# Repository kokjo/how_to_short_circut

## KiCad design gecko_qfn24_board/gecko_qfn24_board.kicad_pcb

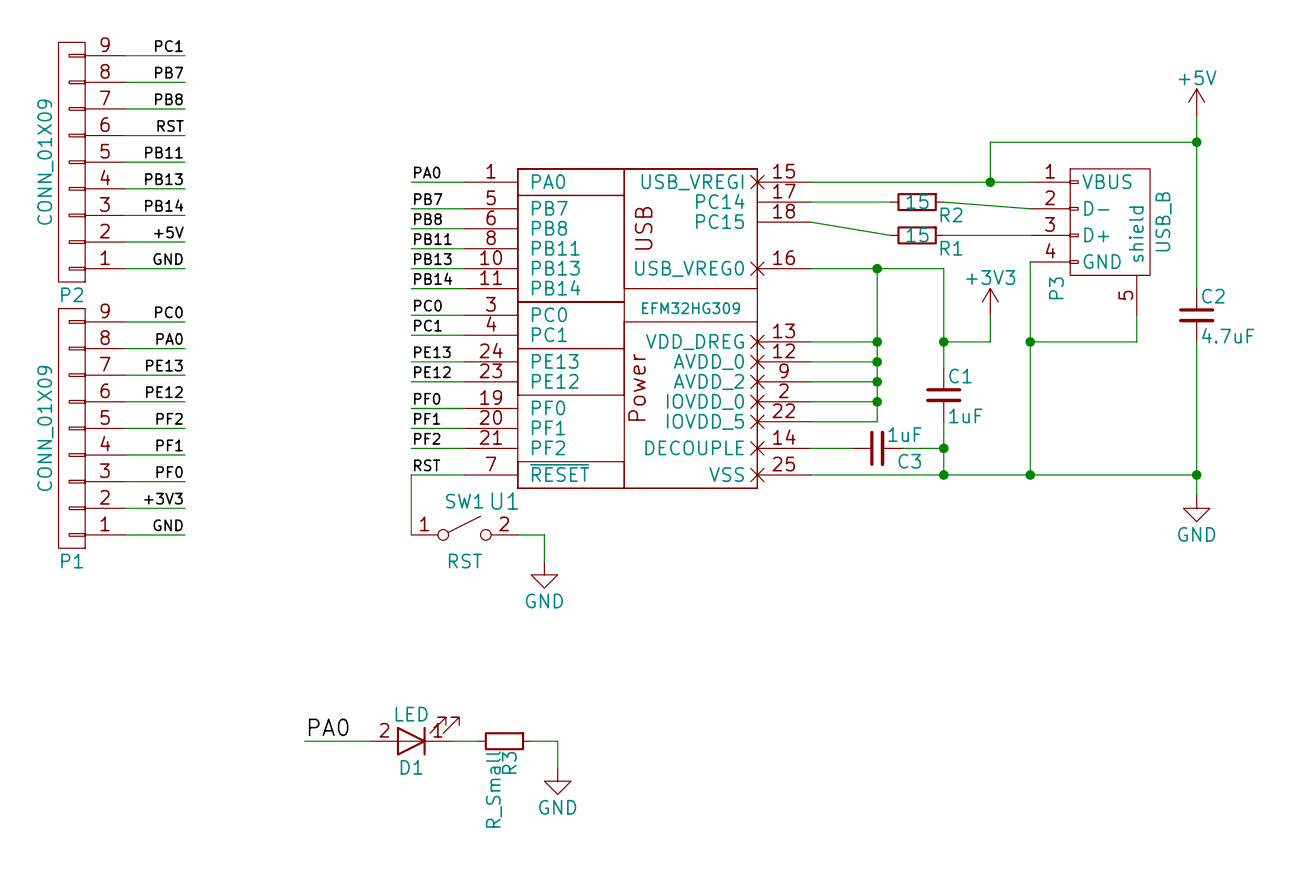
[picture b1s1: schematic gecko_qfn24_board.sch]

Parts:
C1, C3: 1uF; C_0805
C2: 4.7uF; C_0805
D1: LED; LED_0805
P1, P2: CONN_01X09; Pin_Header_Straight_1x09
P3: USB_B; USB_Micro-B_Molex_47346-0001
R1, R2: 15; R_0805
R3: R_Small; R_0805
SW1: RST; SW_SPST_B3U-1000P
U1: EFM32HG309; QFN-24-1EP_5x5mm_Pitch0.65mm

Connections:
+3V3: C1.1, P1.2, U1.2 (IOVDD_0), U1.9 (AVDD_2), U1.12 (AVDD_0), U1.13 (VDD_DREG), U1.16 (USB_VREG0), U1.22 (IOVDD_5); also elsewhere on the board
+5V: C2.1, P2.2, P3.1 (VBUS), U1.15 (USB_VREGI); also elsewhere on the board
/PA0: D1.2 (A), P1.8, U1.1 (PA0); also elsewhere on the board
/PB7: P2.8, U1.5 (PB7); also elsewhere on the board
/PB8: P2.7, U1.6 (PB8); also elsewhere on the board
/PB11: P2.5, U1.8 (PB11); also elsewhere on the board
/PB13: P2.4, U1.10 (PB13); also elsewhere on the board
/PB14: P2.3, U1.11 (PB14); also elsewhere on the board
/PC0: P1.9, U1.3 (PC0); also elsewhere on the board
/PC1: P2.9, U1.4 (PC1); also elsewhere on the board
/PE12: P1.6, U1.23 (PE12); also elsewhere on the board
/PE13: P1.7, U1.24 (PE13); also elsewhere on the board
/PF0: P1.3, U1.19 (PF0); also elsewhere on the board
/PF1: P1.4, U1.20 (PF1); also elsewhere on the board
/PF2: P1.5, U1.21 (PF2); also elsewhere on the board
/RST: P2.6, SW1.1 (A), U1.7 (~RESET); also elsewhere on the board
GND: C1.2, C2.2, C3.2, P1.1, P2.1, P3.4 (GND), P3.5 (shield), R3.1, SW1.2 (B), U1.25 (VSS); also elsewhere on the board
unnamed 17: C3.1, U1.14 (DECOUPLE); also elsewhere on the board
unnamed: D1.1 (K), R3.2
unnamed: P3.2 (D-), R2.1
unnamed: P3.3 (D+), R1.1
unnamed 21: R1.2, U1.18 (PC15); also elsewhere on the board
unnamed 22: R2.2, U1.17 (PC14); also elsewhere on the board

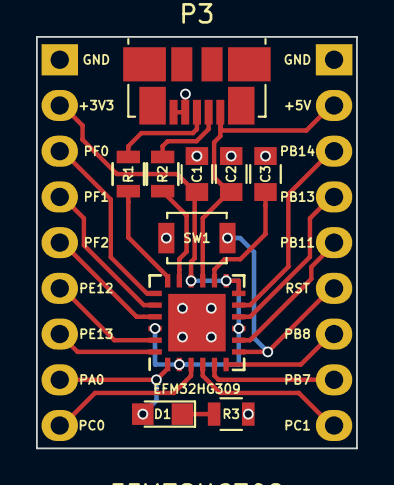
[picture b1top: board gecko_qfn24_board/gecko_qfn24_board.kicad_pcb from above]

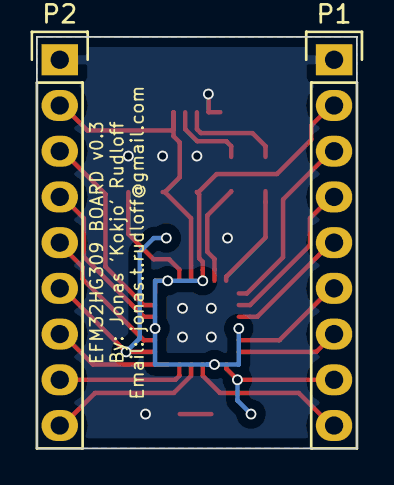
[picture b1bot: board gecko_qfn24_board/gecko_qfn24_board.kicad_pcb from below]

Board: 2 copper layers, 17.8 x 22.9 mm, 12 parts (2 on the bottom side), 23 nets.

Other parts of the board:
EFM32HG309: EFM32HG309; QFN-24-1EP_5x5mm_Pitch0.65mm

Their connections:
+3V3: EFM32HG309.2, EFM32HG309.9, EFM32HG309.12, EFM32HG309.13, EFM32HG309.16, EFM32HG309.22; also elsewhere on the board
+5V: EFM32HG309.15; also elsewhere on the board
/PA0: EFM32HG309.1; also elsewhere on the board
/PB7: EFM32HG309.5; also elsewhere on the board
/PB8: EFM32HG309.6; also elsewhere on the board
/PB11: EFM32HG309.8; also elsewhere on the board
/PB13: EFM32HG309.10; also elsewhere on the board
/PB14: EFM32HG309.11; also elsewhere on the board
/PC0: EFM32HG309.3; also elsewhere on the board
/PC1: EFM32HG309.4; also elsewhere on the board
/PE12: EFM32HG309.23; also elsewhere on the board
/PE13: EFM32HG309.24; also elsewhere on the board
/PF0: EFM32HG309.19; also elsewhere on the board
/PF1: EFM32HG309.20; also elsewhere on the board
/PF2: EFM32HG309.21; also elsewhere on the board
/RST: EFM32HG309.7; also elsewhere on the board
GND: EFM32HG309.25; also elsewhere on the board
unnamed 17: EFM32HG309.14; also elsewhere on the board
unnamed 21: EFM32HG309.18; also elsewhere on the board
unnamed 22: EFM32HG309.17; also elsewhere on the board

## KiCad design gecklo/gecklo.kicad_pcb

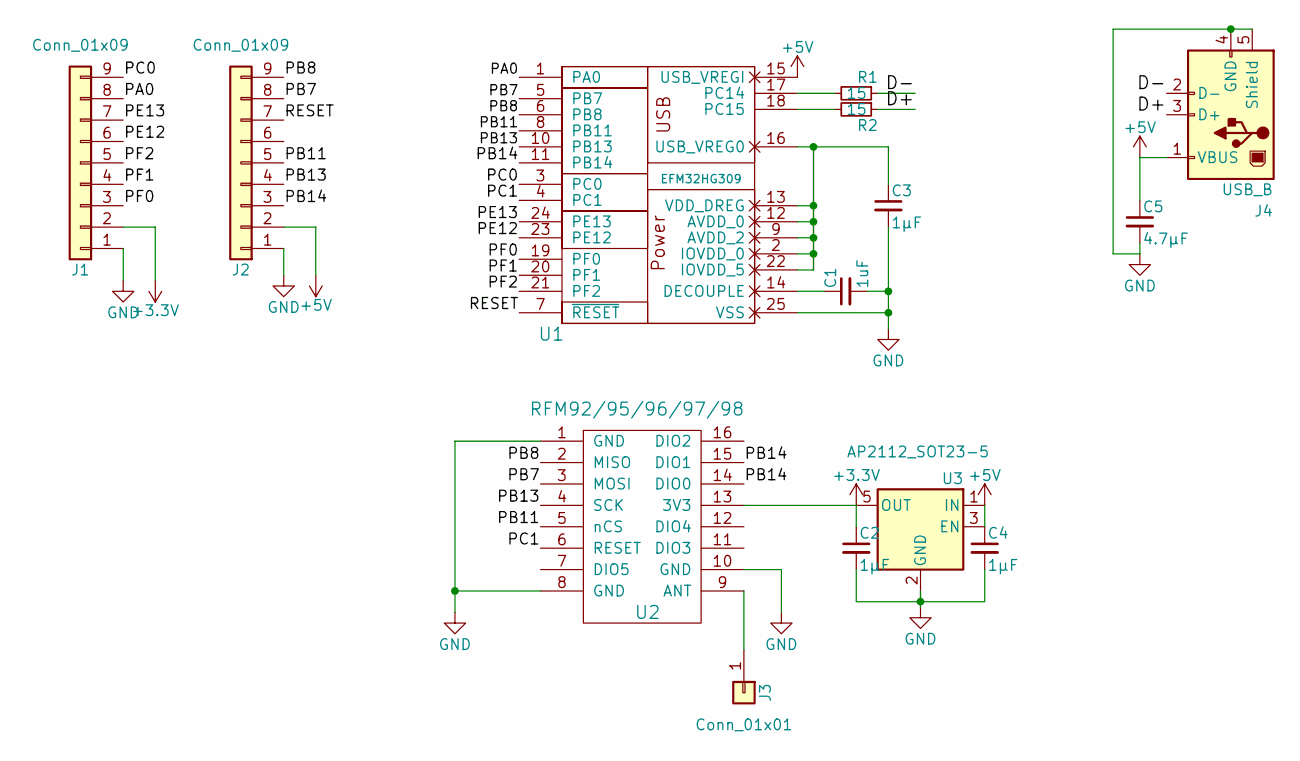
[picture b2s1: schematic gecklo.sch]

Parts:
C1: 1uF; C_0805
C2, C3, C4: 1µF; C_0805
C5: 4.7µF; C_0805
J1, J2: Conn_01x09; Pin_Header_Straight_1x09_Pitch2.54mm
J3: Conn_01x01; Pin_Header_Straight_1x01_Pitch2.54mm
J4: USB_B; USB_Micro-B_Molex_47346-0001
R1, R2: 15; R_0805
U1: EFM32HG309; QFN-24-1EP_5x5mm_Pitch0.65mm
U2: RFM92/95/96/97/98; RFM92_95_96_98
U3: AP2112_SOT23-5; SOT-23-5

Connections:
+3V3: C2.1, J1.2, U2.13 (3V3), U3.4 (NC), U3.5 (OUT)
+5V: C4.1, C5.1, J2.2, J4.1 (VBUS), U1.15 (USB_VREGI), U3.1 (IN), U3.3 (EN)
/D+: J4.3 (D+), R2.1
/D-: J4.2 (D-), R1.1
/PA0: J1.8, U1.1 (PA0)
/PB7: J2.8, U1.5 (PB7), U2.3 (MOSI)
/PB8: J2.9, U1.6 (PB8), U2.2 (MISO)
/PB11: J2.5, U1.8 (PB11), U2.5 (nCS)
/PB13: J2.4, U1.10 (PB13), U2.4 (SCK)
/PB14: J2.3, U1.11 (PB14), U2.14 (DIO0), U2.15 (DIO1)
/PC0: J1.9, U1.3 (PC0)
/PC1: U1.4 (PC1), U2.6 (RESET)
/PE12: J1.6, U1.23 (PE12)
/PE13: J1.7, U1.24 (PE13)
/PF0: J1.3, U1.19 (PF0)
/PF1: J1.4, U1.20 (PF1)
/PF2: J1.5, U1.21 (PF2)
/RESET: J2.7, U1.7 (~RESET)
GND: C1.2, C2.2, C3.2, C4.2, C5.2, J1.1, J2.1, J4.4 (GND), J4.5 (Shield), U1.25 (VSS), U2.1 (GND), U2.8 (GND), U2.10 (GND), U3.2 (GND)
unnamed: C1.1, U1.14 (DECOUPLE)
unnamed: C3.1, U1.2 (IOVDD_0), U1.9 (AVDD_2), U1.12 (AVDD_0), U1.13 (VDD_DREG), U1.16 (USB_VREG0), U1.22 (IOVDD_5)
unnamed: J3.1, U2.9 (ANT)
unnamed: R1.2, U1.17 (PC14)
unnamed: R2.2, U1.18 (PC15)

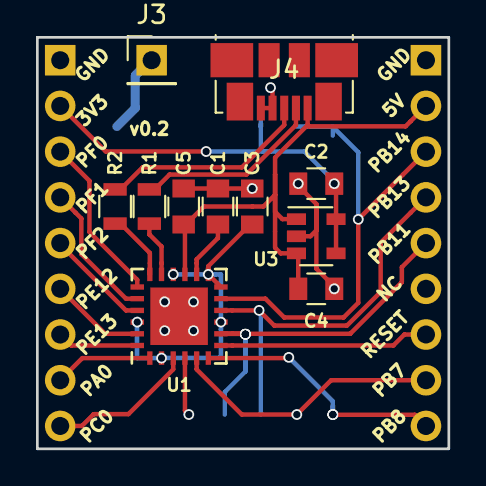
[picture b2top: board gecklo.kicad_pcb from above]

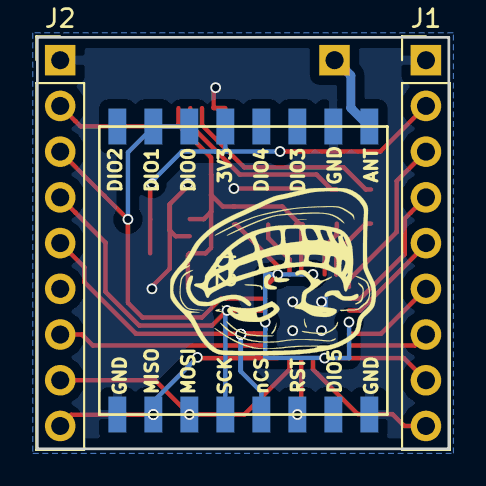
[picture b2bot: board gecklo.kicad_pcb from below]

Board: 2 copper layers, 22.9 x 22.9 mm, 14 parts (3 on the bottom side), 24 nets.

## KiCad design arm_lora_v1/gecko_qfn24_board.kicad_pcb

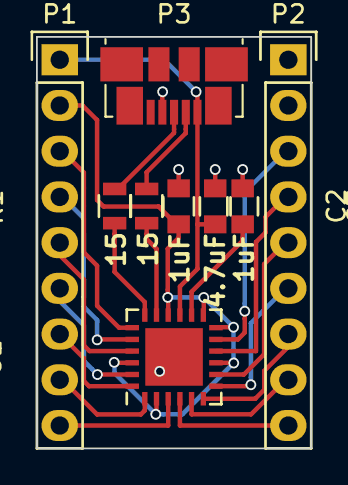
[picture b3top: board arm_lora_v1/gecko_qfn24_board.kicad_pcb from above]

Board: 2 copper layers, 15.2 x 22.9 mm, 9 parts (0 on the bottom side), 22 nets.

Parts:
C1, C2: 1uF; C_0805
C3: 4.7uF; C_0805
P1, P2: CONN_01X09; Pin_Header_Straight_1x09
P3: USB_B; USB_Micro-B_Molex_47346-0001
R1, R2: 15; R_0805
U1: EFM32HG309; QFN-24-1EP_5x5mm_Pitch0.65mm

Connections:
+3V3: C2.1, P1.2, U1.2, U1.9, U1.12, U1.13, U1.16, U1.22
+5V: C3.1, P1.1, P3.1, U1.15
GND: C1.2, C2.2, C3.2, P2.1, P2.2, P3.4, U1.25
unnamed: C1.1, U1.14
unnamed: P1.3, U1.19
unnamed: P1.4, U1.20
unnamed: P1.5, U1.21
unnamed: P1.6, U1.23
unnamed: P1.7, U1.24
unnamed: P1.8, U1.1
unnamed: P1.9, U1.3
unnamed: P2.3, U1.11
unnamed: P2.4, U1.10
unnamed: P2.5, U1.8
unnamed: P2.6, U1.7
unnamed: P2.7, U1.6
unnamed: P2.8, U1.5
unnamed: P2.9, U1.4
unnamed: P3.2, R1.1
unnamed: P3.3, R2.1
unnamed: R1.2, U1.17
unnamed: R2.2, U1.18

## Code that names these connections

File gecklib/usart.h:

#ifndef __USART__
#define __USART__

#include <stdint.h>

#include "mcu.h"
#include "config.h"

void init_usart0();
uint8_t usart0_transfer_byte(uint8_t data);
void usart0_transfer(uint8_t* ch, size_t len);
#if ENABLE_USART0
    #if USART0_LOCATION == USART_ROUTE_LOCATION_LOC3
        #define USART0_CLK  (PC15)
        #define USART0_SS   (PC14)
        #define USART0_MISO (PE12)
        #define USART0_MOSI (PE13)
    #elif USART0_LOCATION == USART_ROUTE_LOCATION_LOC4
        #define USART0_CLK  (PB13)
        #define USART0_SS   (PB14)
        #define USART0_MISO (PB8)
        #define USART0_MOSI (PB7)
    #elif USART0_LOCATION == USART_ROUTE_LOCATION_LOC5
        #define USART0_CLK  (PB13)
        #define USART0_SS   (PB14)
        #define USART0_MISO (PC1)
        #define USART0_MOSI (PC0)
    #elif USART0_LOCATION == USART_ROUTE_LOCATION_LOC6
        #define USART0_CLK  (PE12)
        #define USART0_SS   (PE13)
        #define USART0_MISO (PC1)
        #define USART0_MOSI (PC0)
    #else
        #error "PLEASE fix usart.h"
    #endif
#else
    #define USART0_CLK  (0)
    #define USART0_SS   (0)
    #define USART0_MISO (0)
    #define USART0_MOSI (0)
#endif

#endif

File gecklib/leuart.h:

#ifndef LEUART_H
#define LEUART_H

#include "config.h"

void init_leuart0();
void leuart0_putchar(char ch);
char leuart0_getchar();
void leuart0_puts(char *s);
void leuart0_printf(const char *fmtstr, ...);

#if LEUART0_LOCATION == LEUART_ROUTE_LOCATION_LOC1
    #define LEUART0_RX (PB14)
    #define LEUART0_TX (PB13)
#elif LEUART0_LOCATION == LEUART_ROUTE_LOCATION_LOC3
    #define LEUART0_RX (PF1)
    #define LEUART0_TX (PF0)
#elif LEUART0_LOCATION == LEUART_ROUTE_LOCATION_LOC4
    #define LEUART0_RX (PA0)
    #define LEUART0_TX (PF2)
#elif LEUART0_LOCATION == LEUART_ROUTE_LOCATION_LOC5
    #define LEUART0_RX (PC15)
    #define LEUART0_TX (PC14)
#else
    #error "Fix leuart.h"
#endif

#endif

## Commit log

2018-01-16 initial commit, .gitignore
2018-02-27 commited design for test board
2018-02-27 added minimal teensy-lc development env..
2018-02-27 added tomu-bootloader module
2018-02-27 Added reference manual
2018-02-28 updated bootloader submodule
2018-03-02 minimal blinky example, not using Gecko SDK
2018-03-06 leuart & adc example
2018-03-06 Added USUART code
2018-03-13 add more docs
2018-03-13 moare docz
2018-03-24 leuart suff
2018-03-24 deleted backup file
2018-04-05 Lolz, commit hist. for nerds
2018-04-05 Work
2018-04-10 added spi leuart bridge + doit.py
2018-04-10 better stuff
2018-04-10 Added recv
2018-04-10 seperated radio stuff into seperate file. more java like
2018-04-11 *.bin and *.pyc in .gitignore
2018-04-11 better doit_rfm95_send.py
2018-04-11 updated leuart implementation for rfm95_example
2018-04-12 Cleaned project
2018-04-12 Fixed missing definition
2018-04-12 Added recv code
2018-04-19 Modified for new boards
2018-04-20 made better gecklo board v0.2
2018-04-24 upload the right referance manual for efm32hg309
2018-04-24 Added CMAC and unit tests
2018-04-26 added arm debug documentation
2018-04-26 fixed printf
